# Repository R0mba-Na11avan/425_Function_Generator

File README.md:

# Function Generator (ECE 425)

Firmware for a two-channel function generator built around an ESP32-S3
(N16R8). Per channel, an AD9833 produces the waveform, a TS5A23157 switch picks
the sine/triangle or square path and an AD5452 multiplying DAC sets the
amplitude; one MCP4822 DAC sets both channels' DC offsets (see
`docs/parts.md` for the output stage, `docs/pinout_table.md` for the wiring).
The ESP32 provides three ways to control it:

- **Local:** an ILI9341 LCD dashboard with a rotary encoder and touchscreen
- **AI agents:** an MCP server over Wi-Fi (required for the project)
- **Browser:** a control page at `http://funcgen.local/` on the same Wi-Fi
- **Bluetooth (BLE):** a GATT service a phone can read, write and subscribe to
  (tested with nRF Connect), paired with a passkey shown on the LCD

oui oui baugette

## Architecture

```mermaid
flowchart LR
    LCD["LCD + encoder + touch"]
    MCP["MCP server (HTTP)"]
    WEB["Web page + /api (HTTP)"]
    BLE["BLE (NimBLE)"]
    CTRL["FuncGenController<br/>(mutex, listeners)"]
    FG["FunctionGenerator (CH1)"]
    FG2["FunctionGenerator (CH2)"]
    HW["AD9833 + AD5452 + MCP4822<br/>+ path switch"]

    LCD --> CTRL
    MCP --> CTRL
    WEB --> CTRL
    BLE --> CTRL
    CTRL --> FG --> HW
    CTRL --> FG2 --> HW
```

Every interface is a client of `FuncGenController`. It drives both channels,
serializes access to the hardware (each interface runs in its own task, and
both channels share one SPI bus) and notifies listeners when a channel's state
changes, so the LCD always shows what an agent, phone or browser just set. It
also runs the mirror (LINK: CH2 follows CH1). Nothing outside `core/` touches
`FunctionGenerator` directly.

## Layout

```
425_Function_Generator.ino   creates and wires everything in setup(), loop() deletes itself
src/
  config.h   pins, limits, task settings, network constants
  libs/      vendored third-party libs (AD9833, Adafruit GFX + ILI9341,
             XPT2046_Touchscreen, ArduinoJson) + our own AD5452 and MCP4822 drivers
  core/      FunctionGenerator, FuncGenState, FuncGenController
  core/      ... + net_status.h / ble_status.h (Wi-Fi and BLE state shared by comms and ui)
  core/      ... + safe_pins (control pins to their safe levels, first thing in setup())
  ui/        display_ui (UI task, canvases, listener), dashboard_view (drawing),
             dashboard_logic (layout, formatting, editor), input (encoder + touch),
             input_logic (debounce/accel/tap/hold), boot_screen (Wi-Fi + phones reset countdown).
             the *_logic/_view files are host-tested
  comms/     wifi_manager (+ wifi_logic state machine, provisioning routes),
             http_server, mcp_server, rest_api (web control endpoints),
             api_json (state JSON + Origin check shared by MCP and REST),
             ble_service (+ ble_logic GATT layout and encoding)
  web/       provisioning_html.h (Wi-Fi setup page), index_html.h (control page),
             GENERATED from the top-level web/ folder, don't edit
web/         the pages as plain HTML/CSS/JS (control/, setup/). after a change run
             python tools/embed_web.py (see web/README.md)
tools/       embed_web.py (web/ -> src/web/*_html.h), gen_intellisense.py
```

Dependencies only point downward: `ui`/`comms` -> `core` -> `libs`. `ui` and
`comms` never include each other.

Arduino IDE compiles `src/` recursively but only searches `src/` roots for
headers, so include across folders with relative paths (`"../core/..."`).

## Status

| Part | State |
|---|---|
| `FunctionGenerator` (AD9833 + AD5452 + MCP4822 + path switch) | done (incl. output enable, DC offset, peak limit and limit getters), host-tested, calibration values in `config.h` are placeholders until the output stage is measured |
| `FuncGenController` / `FuncGenState` (two channels, mirror) | done, host-tested |
| `core/safe_pins` (relays open, every generator chip deselected, path switches on the divided path from the top of `setup()`) + both channels reset at boot | done, host-tested against a fake that drops writes to unclaimed pins like ESP32 core 3.x, not tried on hardware yet |
| `ui/input` (encoder via PCNT, button, XPT2046 touch) | done, not tried on hardware yet, touch calibration is a placeholder |
| `ui/display_ui` (dashboard with CH1/CH2 tabs and LINK, editing, info panel with Wi-Fi/phone buttons, remote-change flash, pairing popup) | done, logic and drawing host-tested (screens in `test/build/screens`), not tried on hardware yet |
| `425_Function_Generator.ino` (wiring, boot-time Wi-Fi + phones reset) | done, compiled, not tried on hardware yet |
| `comms/http_server` (shared esp_http_server + route table) | done, host-tested against a fake httpd, not tried on hardware yet |
| `comms/wifi_manager` (STA, AP fallback, setup page, mDNS, NVS) | done, state machine and setup routes host-tested, radio part only compiled, not tried on hardware yet |
| `comms/mcp_server` (JSON-RPC, 9 tools, both channels) | done, host-tested end to end against a fake httpd, not tried on hardware yet |
| `comms/ble_service` (NimBLE GATT, passkey pairing, notifications) | CH1 only (CH2 layout still to be decided), done, encoding and range checks host-tested, the stack part only compiled, not tried on hardware yet |
| `comms/rest_api` + `web/index_html.h` (web control page with a CH1/CH2 switch and Link, `/api/state`, `/api/info`) | done, API host-tested end to end against a fake httpd, page JS only syntax-checked, not tried in a browser against hardware yet |

Suggested order: `config.h` -> display + input -> Wi-Fi + HTTP server (STA, then
AP fallback + provisioning page) -> MCP server -> BLE.

## Design decisions

- **No LVGL.** The dashboard is a single screen drawn directly with Adafruit GFX,
  redrawing only the fields that changed.
- **Two channels:** one controller drives both (`CHANNEL_1`/`CHANNEL_2` in
  code, 1 and 2 in MCP and the web API, where the channel is required so a
  client never changes the wrong output by leaving it out). The LCD shows one
  channel's full dashboard at a time with both channels summed up in a tab row.
- **Mirror (LINK):** CH2 follows CH1's waveform, frequency, amplitude, offset
  and phase; each output's on/off stays its own. Turning it on copies CH1 to
  CH2 right away. While it is on, those CH2 settings are locked everywhere
  (greyed on the LCD, an error over MCP and the web API) instead of quietly
  ending the link. The two AD9833s have their own crystals, so CH2 drifts
  against CH1 in phase; the mirror copies settings, not a phase lock.
- **Wi-Fi:** join the saved network (STA) and fall back to an access point with a
  setup page when that fails, so credentials can be changed without reflashing.
  Credentials are stored in NVS and the device is reachable at `funcgen.local`.
  The setup routes only exist in AP mode. In AP mode with saved credentials it
  tries the saved network again every 5 minutes while nobody is on the AP.
  To change networks, "Change Wi-Fi" in the info panel opens setup mode while
  running (the old network stays saved until a new one is saved). The page is
  never served on the normal network, so a change always needs someone at the
  device.
- **MCP:** Streamable HTTP at `POST /mcp`, stateless, basic tools, **no auth**
  (trusted bench network). Revisit if it is ever exposed more widely.
  Out-of-range values are rejected with a tool error (the LCD clamps instead).
  Requests need `Content-Type: application/json`, and a browser `Origin` must be
  `funcgen.local` or an IP address, so another web site can't drive the generator.
- **Web control page:** served by the generator itself (one embedded HTML file,
  no CDNs, so it also works on the setup AP). It talks to a small JSON API with
  the same request checks and no auth as MCP. Unlike MCP it **clamps** out-of-range
  values (like the knob) and says so. One setting per POST, so the peak rule
  never depends on the order of two changes. The page polls once a second
  instead of holding a socket open. Plain styling for now.
- **BLE:** NimBLE (built into the ESP32 core) through its C API. The Arduino BLE
  wrapper always answers a write with success, so it couldn't reject bad values.
  Every characteristic needs an encrypted, MITM-authenticated link: a new phone
  has to type the 6-digit passkey shown on the LCD, so only someone who can see
  the screen can pair. Up to 3 phones are remembered (oldest dropped). Values are
  fixed-unit integers and out-of-range writes are rejected, like MCP.
- **Limits live in one place** so the LCD, MCP schemas, `get_limits` and the BLE
  range checks can't disagree.
- **Peak limit:** the output can't swing past `OUTPUT_PEAK_MAX_V`, so
  amplitude / 2 + |offset| has to stay below it. The value being changed stops
  at the edge (knob stops, MCP/BLE get an out-of-range error); the other one is
  never moved. `FuncGenLimits::amplitudeFor` / `dcOffsetFor` give the range
  allowed right now.
- **Safe pins at boot:** `holdSafePinStates()` (`core/safe_pins.*`) is the
  first thing `setup()` does: both output relays open, every generator chip
  deselected, both path switches on the divided square path (safe whatever the
  AD9833s powered up making). Both channels' `begin()` follow straight away
  (AD9833 reset to sine and asleep, amplitude 0, offset 0 V, relay open). The
  path switch always moves to the divided path before
  a square starts and back only after it stops, so a 3.3 V square never
  reaches the direct sine/triangle path.
- **Output off** opens the output relay (the BNC is disconnected), puts the
  AD9833 to sleep and sets both DACs to 0 V. The amplitude and offset are kept
  and come back when the output is turned on. The relay opens first when
  turning off and closes last when turning on, and it stays open from power-on
  until the output is turned on, so the start-up glitch never reaches the BNC.

## Build (Arduino IDE)

Board: ESP32S3 Dev Module, Flash 16MB, PSRAM "OPI PSRAM", Partition Scheme
"16M Flash (3MB APP/9.9MB FATFS)" (the default 1.2 MB app partition is too small
once Wi-Fi and BLE are in).

Libraries: everything is vendored in `src/libs`, so nothing needs installing from
the Library Manager. ArduinoJson is v7.4.3 as the official single-header release
(`ArduinoJson-v7.4.3.h`, renamed; the multi-file version needs the library on the
include path, which the IDE doesn't do for `src/libs`). It is used by the Wi-Fi
setup routes and the MCP server, include it as
`#include "../libs/ArduinoJson/ArduinoJson.h"`.

## Using it

- **Channels:** the row under the status bar has a tab per channel (waveform,
  frequency and ON/OFF of each) and a LINK button. The fields below show the
  filled tab's channel. Tap a tab to show that channel, or select the tabs with
  the knob and press to switch.
- **LINK:** tap it (or select it and press) to make CH2 follow CH1. While it is
  lit, CH2's fields read "LINKED", are greyed and can't be edited (change CH1
  instead); CH2's OUTPUT still works on its own. Tap it again to unlink: CH2
  keeps its values.
- **Knob:** turn to pick a field, press to edit it (press on OUTPUT toggles the
  output), turn to change the value. Long press when done (on amplitude, offset
  and waveform a second press works too). Edit mode also ends after 10 s
  without input.
- **Frequency:** while editing, each press moves the underlined digit to the
  next power of 10 (0.1 Hz, 1 Hz, 10 Hz ... 1 MHz, then back to 0.1 Hz); the
  current step shows as "STEP" in the top right. Turning starts from the value
  on screen. In MHz the 0.1 Hz digit isn't shown, so that step acts as 1 Hz.
- **Touch:** tap a field to select it, tap it again to edit, tap a frequency
  digit to step that digit. Tap the status bar for the network info panel.
- **Remote changes:** a field changed over MCP, BLE or the web page flashes
  magenta and an "MCP", "BLE" or "WEB" badge shows in the status bar for a few
  seconds. If you were
  editing that field, editing stops and your next turn starts from the new value.
  A change to the channel that isn't shown flashes its tab instead.
- **Bluetooth:** a Bluetooth icon at the right of the status bar means a phone is
  connected. When a new phone pairs, a full-screen popup shows the code to type
  on the phone; press or tap to cancel (it cancels itself after 30 s).
- **Power-on:** both channels sine, 1 Hz, 1 Vpp, 0 V offset, output OFF, LINK off, CH1 shown.
- **Amplitude and offset** share one limit: the bigger the amplitude, the less
  offset is allowed (and the other way round). The knob just stops at the edge.
- **Info panel buttons:** turn the knob to highlight "Change Wi-Fi", "Forget
  phones" or "close" and press, or tap them.
  - *Change Wi-Fi* (asks first) opens setup mode; the info panel then shows the
    steps. The current network stays saved until you save a new one. In setup
    mode the button becomes *Back to <network>*, which goes straight back. With
    nobody on the setup Wi-Fi it also goes back by itself after 5 minutes.
  - *Forget phones* (asks first) forgets every paired phone and disconnects the
    connected ones. Also remove FuncGen from each phone's Bluetooth settings.
- **Backup reset:** if the screen or touch isn't usable, hold the knob button
  while powering on, through the 3 s countdown. The saved network and the paired
  phones are forgotten and the generator restarts in setup mode.
- **Serial (115200):** prints the firmware version, every network address
  change and BLE pairing results.

## Connecting an agent

Once the generator is on your network (the LCD shows its address):

    claude mcp add --transport http funcgen http://funcgen.local/mcp

If `funcgen.local` doesn't resolve, use the IP from the LCD instead. To poke at it
by hand, run `npx @modelcontextprotocol/inspector`, choose "Streamable HTTP" and
the same URL (the Inspector's default proxy mode works; its direct mode needs
CORS, which this server doesn't offer).

Tools: `set_waveform`, `set_frequency`, `set_amplitude`, `set_phase`,
`set_dc_offset`, `set_output` (each needs `"channel": 1` or `2`), `set_mirror`
(`{"enabled": true}`: CH2 follows CH1), `get_state` (one channel with
`"channel"`, both without), `get_limits` (shared by both channels).

## Web control page

Open `http://funcgen.local/` (or the IP from the LCD) on any phone or laptop on
the same network. In setup mode `/` is the Wi-Fi setup page; the controls are
at `http://192.168.4.1/control` (the setup page links to them).

- **Controls tab:** CH1/CH2 buttons pick the channel the controls change, and
  Link makes CH2 follow CH1 (CH2's controls, except its output, are disabled
  while it is on). Then output on/off, waveform, and fields for frequency (pick
  Hz/kHz/MHz), amplitude, DC offset and phase. A field is sent when you press
  Enter or leave it; Esc undoes the typing. Amplitude and offset show the range
  allowed right now. A value past the edge is clamped and a note says what was
  set. The sketch shows two cycles of the output against the ±peak limit.
- **Device tab:** firmware, Wi-Fi and Bluetooth info. Changing Wi-Fi and
  forgetting phones stay on the LCD only.
- Changes made elsewhere (knob, MCP, BLE, another browser) show up within about
  a second and flash.

API (JSON, the same names as MCP's `get_state`):

| Route | What |
|---|---|
| `GET /api/state` | `{"channels": [{"state": {...}, "ranges": {...}}, ...], "mirror", "output_peak_v"}`, ranges are the ones allowed right now for that channel |
| `POST /api/state` | exactly one setting plus its channel, e.g. `{"channel": 1, "amplitude_vpp": 2.5}`, `{"channel": 2, "waveform": "square"}`, or `{"mirror": true}` on its own. Answers like GET plus `"clamped"` (and a `"note"` when it was). A mirrored CH2 setting while Link is on gets 409. Needs `Content-Type: application/json` |
| `GET /api/info` | firmware, `poll_ms`, Wi-Fi and BLE status |

    curl -X POST -H "Content-Type: application/json" -d "{\"channel\": 1, \"frequency_hz\": 1000}" http://funcgen.local/api/state

## Connecting a phone (BLE)

1. Install **nRF Connect for Mobile** (Nordic Semiconductor, free on iOS and
   Android) and open it. It scans for nearby devices.
2. Tap **Connect** next to `FuncGen-XXXX` (same name as the setup Wi-Fi; the
   info panel shows it).
3. The phone asks to pair: type the code from the LCD popup. This happens once
   per phone.
4. Open the service `54750f00-...` (CH1; CH2 isn't on BLE yet). Each characteristic is labelled. Tap the up
   arrow to write a value, the triple arrow to get live updates.

| UUID | Setting | Bytes | Unit / values | Example |
|---|---|---|---|---|
| `54750f01-…` | waveform | 1 (u8) | 0 sine, 1 square, 2 triangle | `02` |
| `54750f02-…` | frequency | 4 (u32) | 0.01 Hz | 1 kHz = 100000 = `A0 86 01 00` |
| `54750f03-…` | amplitude | 2 (u16) | mVpp (range depends on waveform and offset) | 2.5 Vpp = 2500 = `C4 09` |
| `54750f04-…` | phase | 2 (u16) | 0.01 degree, 0 to 35999 | 90° = 9000 = `28 23` |
| `54750f05-…` | DC offset | 2 (s16) | mV (range depends on amplitude) | -0.25 V = -250 = `06 FF` |
| `54750f06-…` | output | 1 (u8) | 0 off, 1 on | `01` |

Full UUIDs: `54750fXX-f75a-46c0-b78a-746996b46f1a`. Numbers are little-endian
(nRF Connect can also take them as plain numbers if you pick UINT16/UINT32 in the
write dialog). A wrong size or out-of-range value is refused with an ATT error
(0x0D wrong length, 0xFF out of range).

If a phone says it can't connect after the board's phones were forgotten, remove
the board from the phone's Bluetooth settings and pair again.

## Tests

Host tests run the real core, UI logic and vendored libraries on a PC against
fake Arduino/SPI/FreeRTOS headers (`test/fakes`). They check what would reach
the AD9833, the AD5452, the MCP4822 and the path switch, and render the dashboard with the real Adafruit GFX code
to BMP screenshots in `test/build/screens`. The HTTP server, Wi-Fi state machine
and setup routes run against a fake esp_http_server. The BLE value encoding and
range checks run against the real controller; the NimBLE stack itself isn't
faked. The web API runs end to end like MCP; the page's JavaScript is only
syntax-checked (with `node`, if installed), not run. The script also fails if
`src/web/*_html.h` is older than `web/` (run `python tools/embed_web.py`).
Needs Python and g++ (on Windows:
`scoop install mingw`):

    bash test/run_tests.sh

VS Code IntelliSense: `python tools/gen_intellisense.py` writes
`.vscode/compile_commands.json` from the real ESP32-S3 build flags.

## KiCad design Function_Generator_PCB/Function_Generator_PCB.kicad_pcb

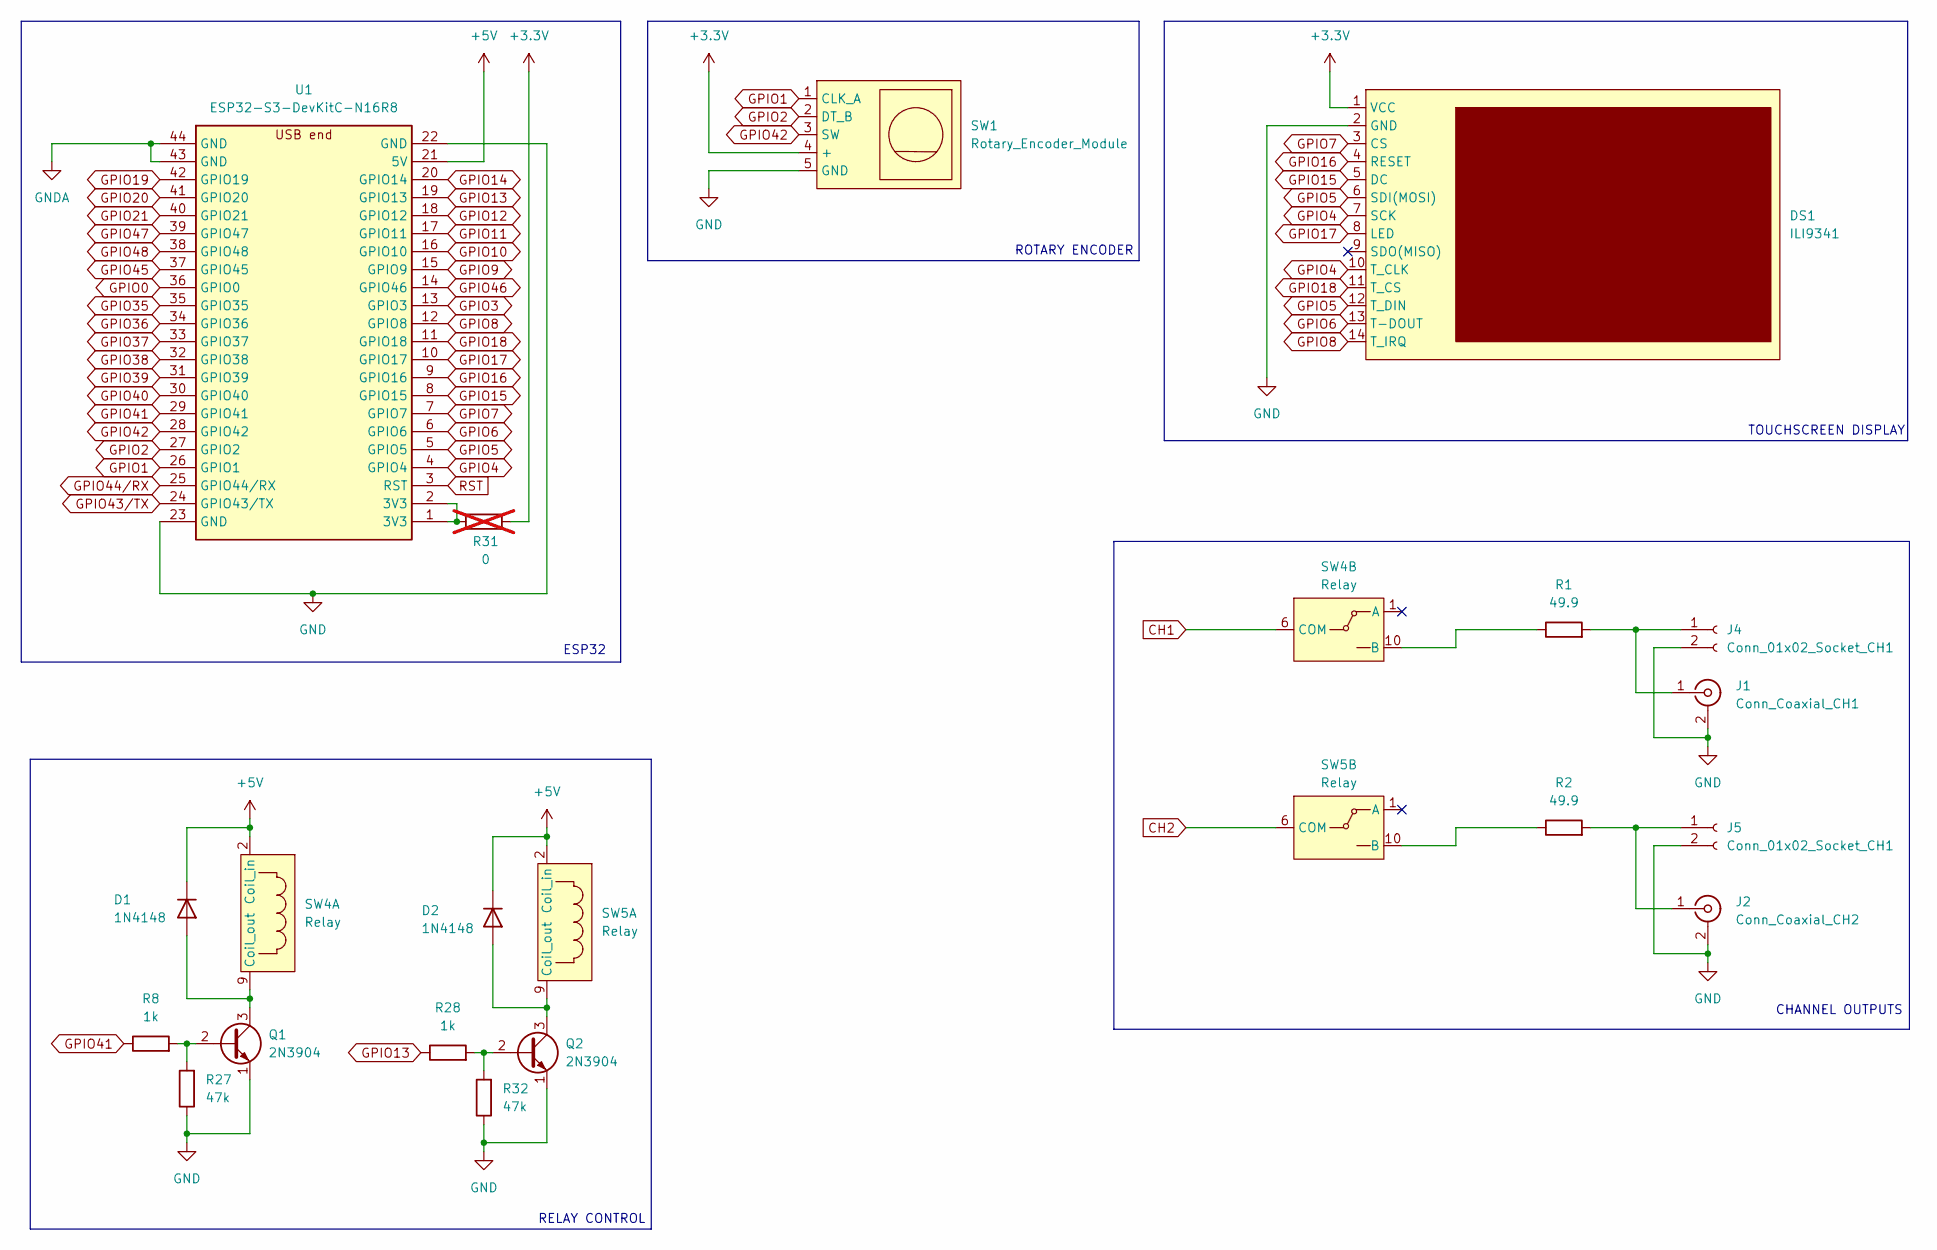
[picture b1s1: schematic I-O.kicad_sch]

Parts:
D1, D2: 1N4148; D_DO-35_SOD27_P7.62mm_Horizontal
DS1: ILI9341; PinSocket_1x14_P2.54mm_Vertical
J1: Conn_Coaxial_CH1; TerminalBlock_MaiXu_MX126-5.0-02P_1x02_P5.00mm
J2: Conn_Coaxial_CH2; TerminalBlock_MaiXu_MX126-5.0-02P_1x02_P5.00mm
J4, J5: Conn_01x02_Socket_CH1; PinSocket_1x02_P2.54mm_Vertical
Q1, Q2: 2N3904; TO-92_Inline
R1, R2: 49.9; R_2512_6332Metric_Pad1.40x3.35mm_HandSolder
R8, R28: 1k; R_0805_2012Metric_Pad1.20x1.40mm_HandSolder
R27, R32: 47k; R_0805_2012Metric_Pad1.20x1.40mm_HandSolder
R31: 0; R_0805_2012Metric_Pad1.20x1.40mm_HandSolder; not fitted
SW1: Rotary_Encoder_Module; PinSocket_1x05_P2.54mm_Vertical
SW4, SW5: Relay; Relay_SPDT_Omron_G5V-1
U1: ESP32-S3-DevKitC-N16R8; ESP32-S3-DevKitC-1_DualUSB

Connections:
+3.3V: DS1.1 (VCC), R31.2, SW1.4 (+); also elsewhere on the board
+5V: D1.1 (K), D2.1 (K), SW4.2 (Coil_in), SW5.2 (Coil_in), U1.21 (5V); also elsewhere on the board
CH1: SW4.6 (COM); also elsewhere on the board
CH2: SW5.6 (COM); also elsewhere on the board
GND: DS1.2 (GND), J1.2 (Ext), J2.2 (Ext), J4.2, J5.2, Q1.1 (E), Q2.1 (E), R27.1, R32.1, SW1.5 (GND), U1.22 (GND), U1.23 (GND), U1.43 (GND), U1.44 (GND); also elsewhere on the board
GPIO0: U1.36 (GPIO0)
GPIO1: SW1.1 (CLK_A), U1.26 (GPIO1)
GPIO2: SW1.2 (DT_B), U1.27 (GPIO2)
GPIO3: U1.13 (GPIO3)
GPIO4: DS1.7 (SCK), DS1.10 (T_CLK), U1.4 (GPIO4)
GPIO5: DS1.6 (SDI(MOSI)), DS1.12 (T_DIN), U1.5 (GPIO5)
GPIO6: DS1.13 (T-DOUT), U1.6 (GPIO6)
GPIO7: DS1.3 (CS), U1.7 (GPIO7)
GPIO8: DS1.14 (T_IRQ), U1.12 (GPIO8)
GPIO9: U1.15 (GPIO9); also elsewhere on the board
GPIO10: U1.16 (GPIO10); also elsewhere on the board
GPIO11: U1.17 (GPIO11); also elsewhere on the board
GPIO12: U1.18 (GPIO12); also elsewhere on the board
GPIO13: R28.1, U1.19 (GPIO13)
GPIO14: U1.20 (GPIO14); also elsewhere on the board
GPIO15: DS1.5 (DC), U1.8 (GPIO15)
GPIO16: DS1.4 (RESET), U1.9 (GPIO16)
GPIO17: DS1.8 (LED), U1.10 (GPIO17)
GPIO18: DS1.11 (T_CS), U1.11 (GPIO18)
GPIO19: U1.42 (GPIO19)
GPIO20: U1.41 (GPIO20)
GPIO21: U1.40 (GPIO21); also elsewhere on the board
GPIO35: U1.35 (GPIO35)
GPIO36: U1.34 (GPIO36)
GPIO37: U1.33 (GPIO37)
GPIO38: U1.32 (GPIO38)
GPIO39: U1.31 (GPIO39); also elsewhere on the board
GPIO40: U1.30 (GPIO40); also elsewhere on the board
GPIO41: R8.1, U1.29 (GPIO41)
GPIO42: SW1.3 (SW), U1.28 (GPIO42)
GPIO43/TX: U1.24 (GPIO43/TX)
GPIO44/RX: U1.25 (GPIO44/RX)
GPIO45: U1.37 (GPIO45)
GPIO46: U1.14 (GPIO46)
GPIO47: U1.39 (GPIO47); also elsewhere on the board
GPIO48: U1.38 (GPIO48)
unnamed: D1.2 (A), Q1.3 (C), SW4.9 (Coil_out)
unnamed: D2.2 (A), Q2.3 (C), SW5.9 (Coil_out)
unnamed: J1.1 (In), J4.1, R1.2
unnamed: J2.1 (In), J5.1, R2.2
unnamed: Q1.2 (B), R8.2, R27.2
unnamed: Q2.2 (B), R28.2, R32.2
unnamed: R31.1, U1.1 (3V3), U1.2 (3V3)
unnamed: R1.1, SW4.10 (B)
unnamed: R2.1, SW5.10 (B)
RST: U1.3 (RST)

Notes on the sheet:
RELAY CONTROL
CHANNEL OUTPUTS
ROTARY ENCODER
ESP32
TOUCHSCREEN DISPLAY

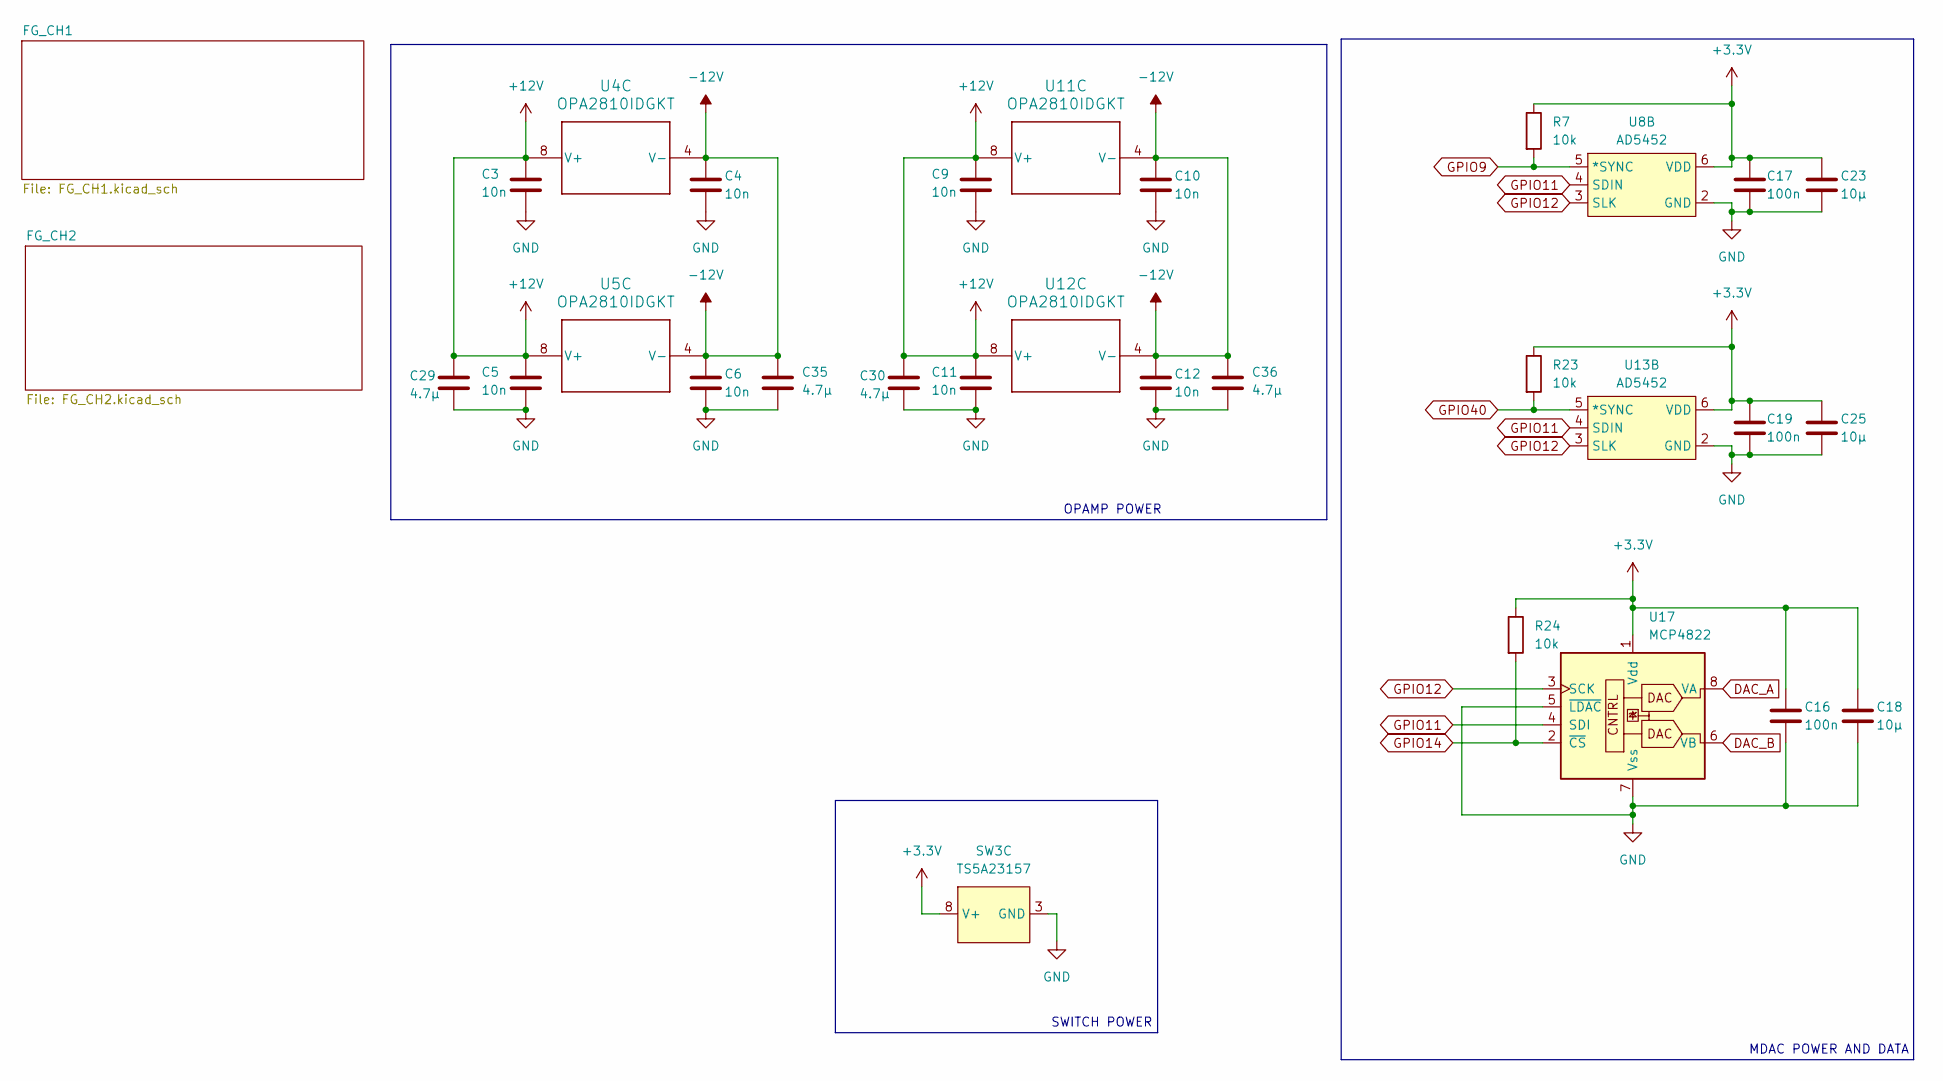
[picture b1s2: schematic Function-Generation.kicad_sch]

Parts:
C3, C4, C5, C6, C9, C10, C11, C12: 10n; C_0805_2012Metric_Pad1.18x1.45mm_HandSolder
C16, C17, C19: 100n; C_0805_2012Metric_Pad1.18x1.45mm_HandSolder
C18, C23, C25: 10μ; C_0805_2012Metric_Pad1.18x1.45mm_HandSolder
C29, C30, C35, C36: 4.7μ; C_1206_3216Metric_Pad1.33x1.80mm_HandSolder
R7, R23, R24: 10k; R_0805_2012Metric_Pad1.20x1.40mm_HandSolder
SW3: TS5A23157; TS5A23157_Module
U4, U5, U11, U12: OPA2810IDGKT; DGK0008A_N
U8, U13: AD5452; RM_8_ADI-M
U17: MCP4822; SOIC8-N_MC_MCH-M

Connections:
+3.3V: C16.1, C17.1, C18.1, C19.1, C23.1, C25.1, R7.1, R23.1, R24.1, SW3.8 (V+), U8.6 (VDD), U13.6 (VDD), U17.1 (Vdd); also elsewhere on the board
+12V: C3.1, C5.1, C9.1, C11.1, C29.1, C30.1, U4.8 (V+), U5.8 (V+), U11.8 (V+), U12.8 (V+); also elsewhere on the board
-12V: C4.1, C6.1, C10.1, C12.1, C35.1, C36.1, U4.4 (V-), U5.4 (V-), U11.4 (V-), U12.4 (V-); also elsewhere on the board
DAC_A: U17.8 (VA); also elsewhere on the board
DAC_B: U17.6 (VB); also elsewhere on the board
GND: C3.2, C4.2, C5.2, C6.2, C9.2, C10.2, C11.2, C12.2, C16.2, C17.2, C18.2, C19.2, C23.2, C25.2, C29.2, C30.2, C35.2, C36.2, SW3.3 (GND), U8.2 (GND), U13.2 (GND), U17.5 (~LDAC), U17.7 (Vss); also elsewhere on the board
GPIO9: R7.2, U8.5 (*SYNC); also elsewhere on the board
GPIO11: U8.4 (SDIN), U13.4 (SDIN), U17.4 (SDI); also elsewhere on the board
GPIO12: U8.3 (SLK), U13.3 (SLK), U17.3 (SCK); also elsewhere on the board
GPIO14: R24.2, U17.2 (~CS); also elsewhere on the board
GPIO40: R23.2, U13.5 (*SYNC); also elsewhere on the board

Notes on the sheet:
OPAMP POWER
MDAC POWER AND DATA
SWITCH POWER

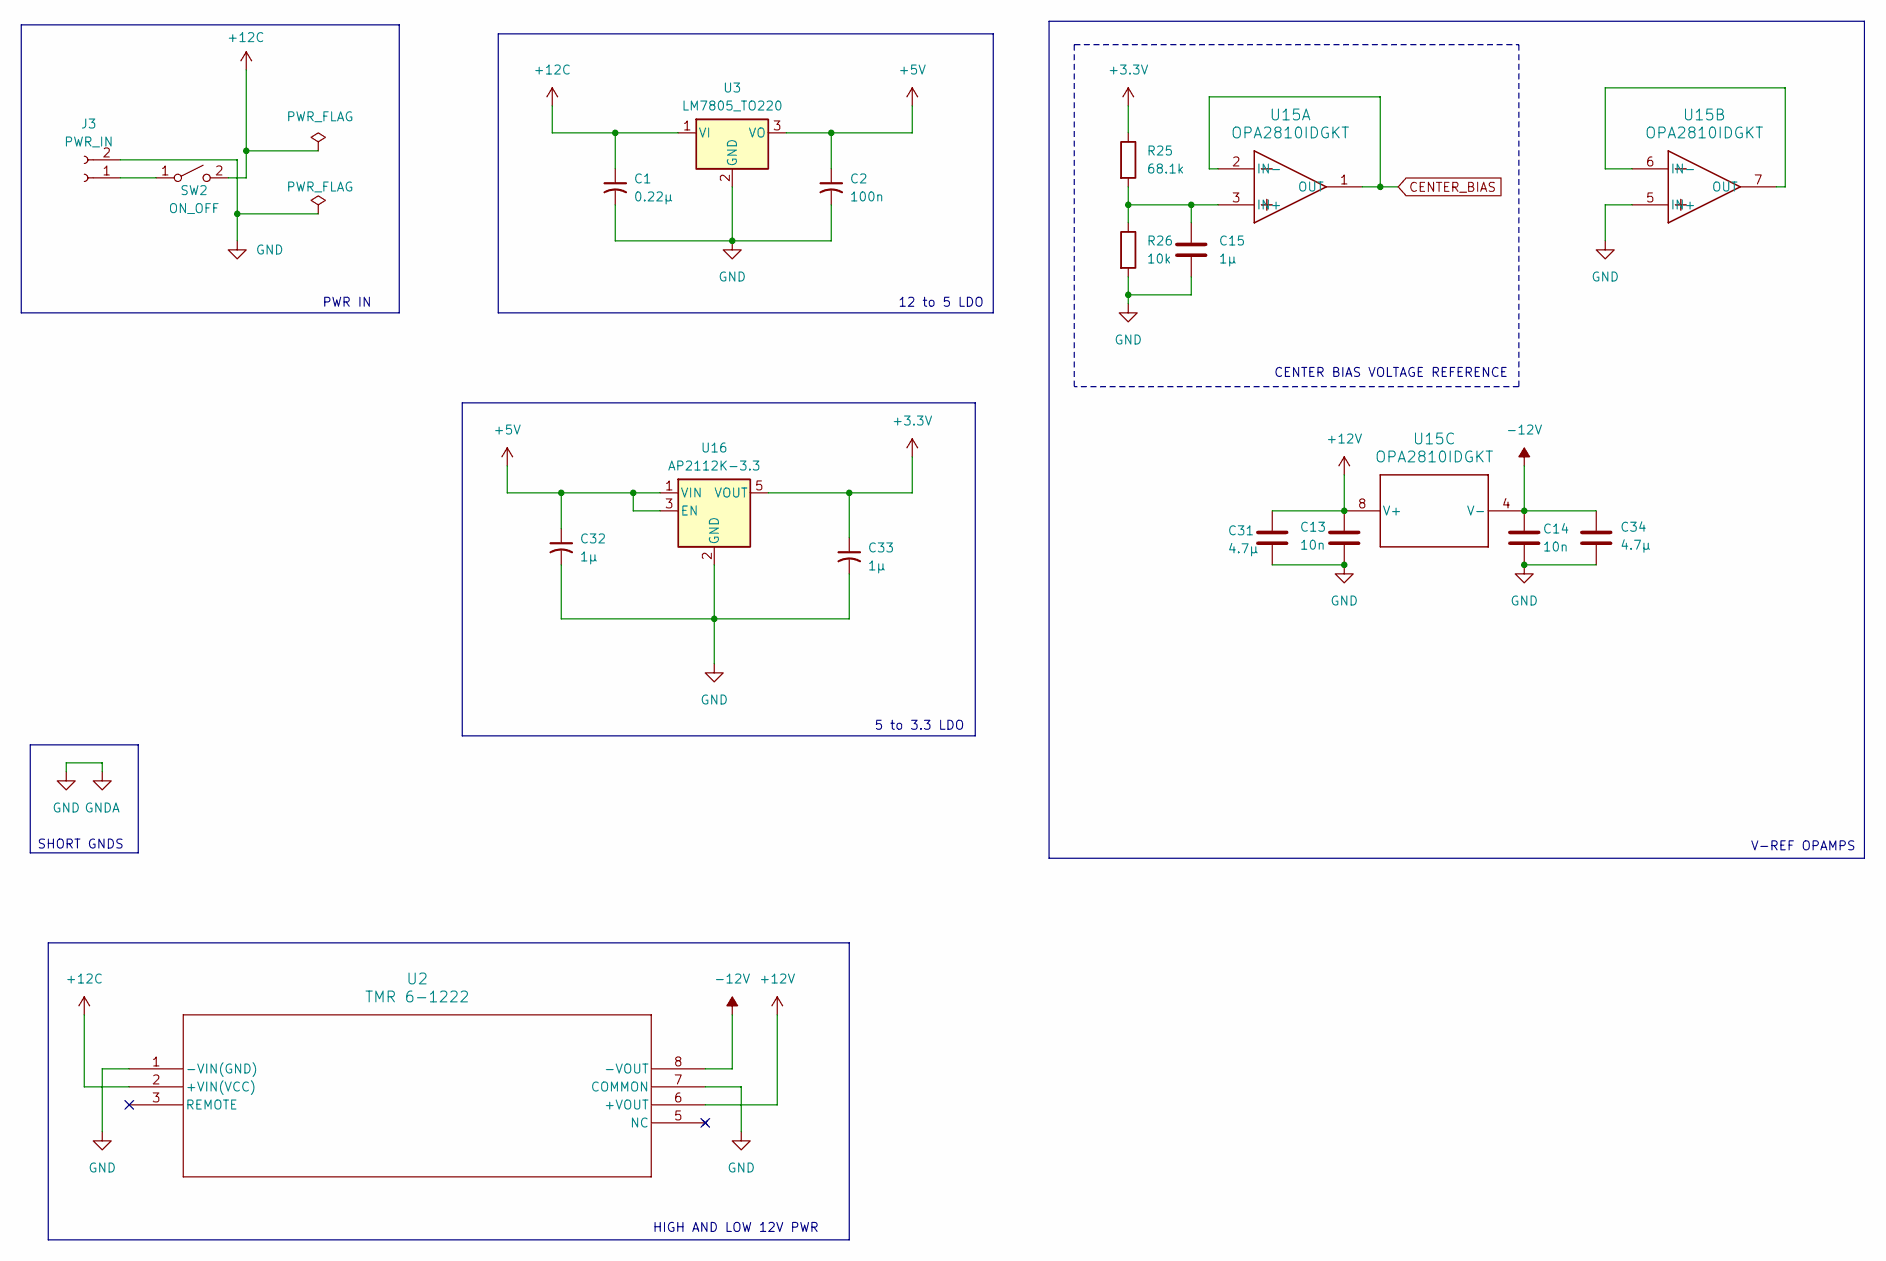
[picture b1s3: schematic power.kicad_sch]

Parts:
C1: 0.22μ; C_0805_2012Metric_Pad1.18x1.45mm_HandSolder
C2: 100n; C_0805_2012Metric_Pad1.18x1.45mm_HandSolder
C13, C14: 10n; C_0805_2012Metric_Pad1.18x1.45mm_HandSolder
C15, C32, C33: 1μ; C_0805_2012Metric_Pad1.18x1.45mm_HandSolder
C31, C34: 4.7μ; C_1206_3216Metric_Pad1.33x1.80mm_HandSolder
J3: PWR_IN; BarrelJack_CUI_PJ-102AH_Horizontal
R25: 68.1k; R_0805_2012Metric_Pad1.20x1.40mm_HandSolder
R26: 10k; R_0805_2012Metric_Pad1.20x1.40mm_HandSolder
SW2: ON_OFF; SolderWire-0.5sqmm_1x02_P4.6mm_D0.9mm_OD2.1mm_Relief
U2: TMR 6-1222; TMR 6_TRP
U3: LM7805_TO220; TO-220-3_Vertical
U15: OPA2810IDGKT; DGK0008A_N
U16: AP2112K-3.3; SOT-23-5

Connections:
+3.3V: C33.1, R25.1, U16.5 (VOUT); also elsewhere on the board
+5V: C2.1, C32.1, U3.3 (VO), U16.1 (VIN), U16.3 (EN); also elsewhere on the board
+12C: C1.1, SW2.2 (B), U2.2 (+VIN(VCC)), U3.1 (VI)
+12V: C13.1, C31.1, U2.6 (+VOUT), U15.8 (V+); also elsewhere on the board
-12V: C14.1, C34.1, U2.8 (-VOUT), U15.4 (V-); also elsewhere on the board
CENTER_BIAS: U15.1 (OUT), U15.2 (IN-); also elsewhere on the board
GND: C1.2, C2.2, C13.2, C14.2, C15.2, C31.2, C32.2, C33.2, C34.2, J3.2, R26.2, U2.1 (-VIN(GND)), U2.7 (COMMON), U3.2 (GND), U15.5 (IN+), U16.2 (GND); also elsewhere on the board
unnamed: J3.1, SW2.1 (A)
unnamed: C15.1, R25.2, R26.1, U15.3 (IN+)
unnamed: U15.6 (IN-), U15.7 (OUT)

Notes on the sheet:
12 to 5 LDO
CENTER BIAS VOLTAGE REFERENCE
5 to 3.3 LDO
PWR IN
V-REF OPAMPS
SHORT GNDS
HIGH AND LOW 12V PWR

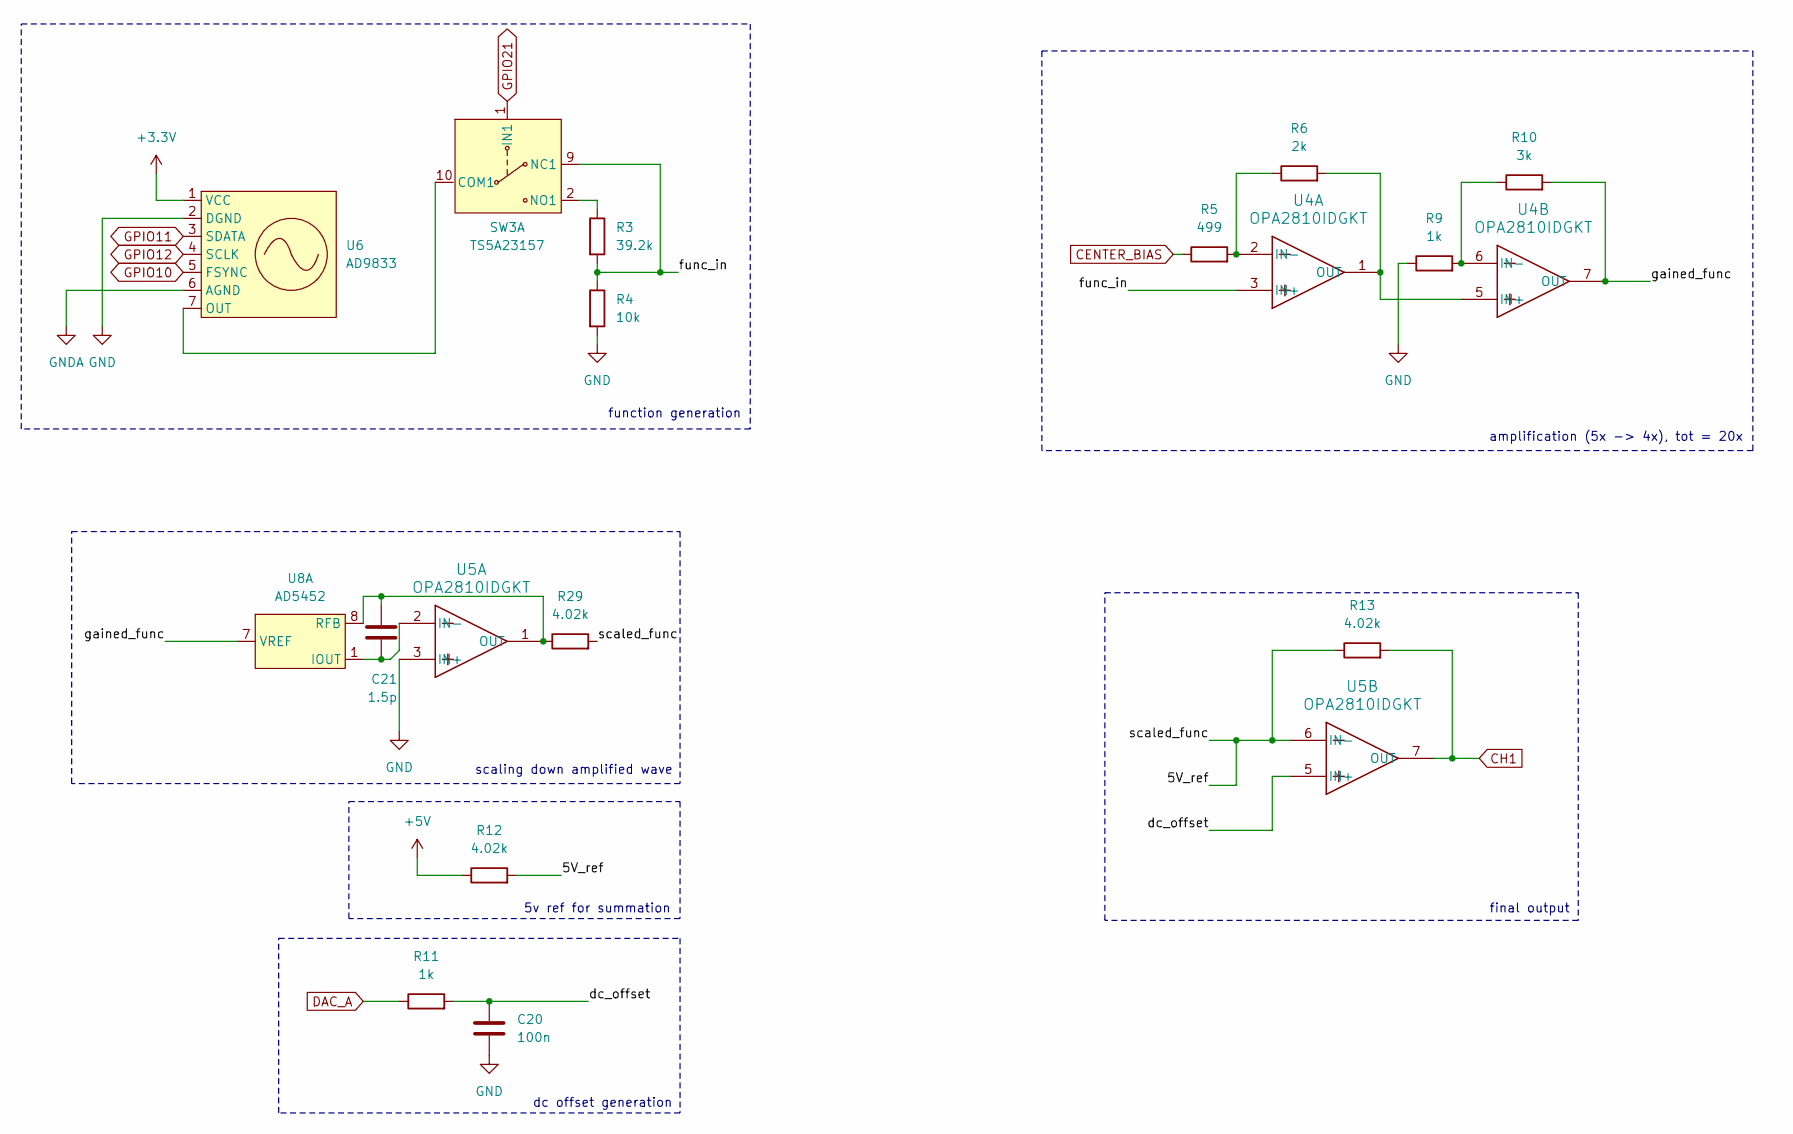
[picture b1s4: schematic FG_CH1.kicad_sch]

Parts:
C20: 100n; C_0805_2012Metric_Pad1.18x1.45mm_HandSolder
C21: 1.5p; C_0805_2012Metric_Pad1.18x1.45mm_HandSolder
R3: 39.2k; R_0805_2012Metric_Pad1.20x1.40mm_HandSolder
R4: 10k; R_0805_2012Metric_Pad1.20x1.40mm_HandSolder
R5: 499; R_0805_2012Metric_Pad1.20x1.40mm_HandSolder
R6: 2k; R_0805_2012Metric_Pad1.20x1.40mm_HandSolder
R9, R11: 1k; R_0805_2012Metric_Pad1.20x1.40mm_HandSolder
R10: 3k; R_0805_2012Metric_Pad1.20x1.40mm_HandSolder
R12, R13, R29: 4.02k; R_0805_2012Metric_Pad1.20x1.40mm_HandSolder
SW3: TS5A23157; TS5A23157_Module
U4, U5: OPA2810IDGKT; DGK0008A_N
U6: AD9833; PinSocket_1x07_P2.54mm_Vertical
U8: AD5452; RM_8_ADI-M

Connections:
+3.3V: U6.1 (VCC); also elsewhere on the board
+5V: R12.1; also elsewhere on the board
/Function_Generation/FG_CH1/5V_ref: R12.2, R13.1, R29.2, U5.6 (IN-)
/Function_Generation/FG_CH1/dc_offset: C20.1, R11.2, U5.5 (IN+)
/Function_Generation/FG_CH1/func_in: R3.2, R4.1, SW3.9 (NC1), U4.3 (IN+)
/Function_Generation/FG_CH1/gained_func: R10.2, U4.7 (OUT), U8.7 (VREF)
CENTER_BIAS: R5.1; also elsewhere on the board
CH1: R13.2, U5.7 (OUT); also elsewhere on the board
DAC_A: R11.1; also elsewhere on the board
GND: C20.2, R4.2, R9.1, U5.3 (IN+), U6.2 (DGND), U6.6 (AGND); also elsewhere on the board
GPIO10: U6.5 (FSYNC); also elsewhere on the board
GPIO11: U6.3 (SDATA); also elsewhere on the board
GPIO12: U6.4 (SCLK); also elsewhere on the board
GPIO21: SW3.1 (IN1); also elsewhere on the board
unnamed: SW3.10 (COM1), U6.7 (OUT)
unnamed: R3.1, SW3.2 (NO1)
unnamed: R5.2, R6.1, U4.2 (IN-)
unnamed: R6.2, U4.1 (OUT), U4.5 (IN+)
unnamed: R9.2, R10.1, U4.6 (IN-)
unnamed: C21.2, U5.2 (IN-), U8.1 (IOUT)
unnamed: C21.1, R29.1, U5.1 (OUT), U8.8 (RFB)

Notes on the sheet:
5v ref for summation
function generation
scaling down amplified wave
final output
amplification (5x -> 4x), tot = 20x
dc offset generation

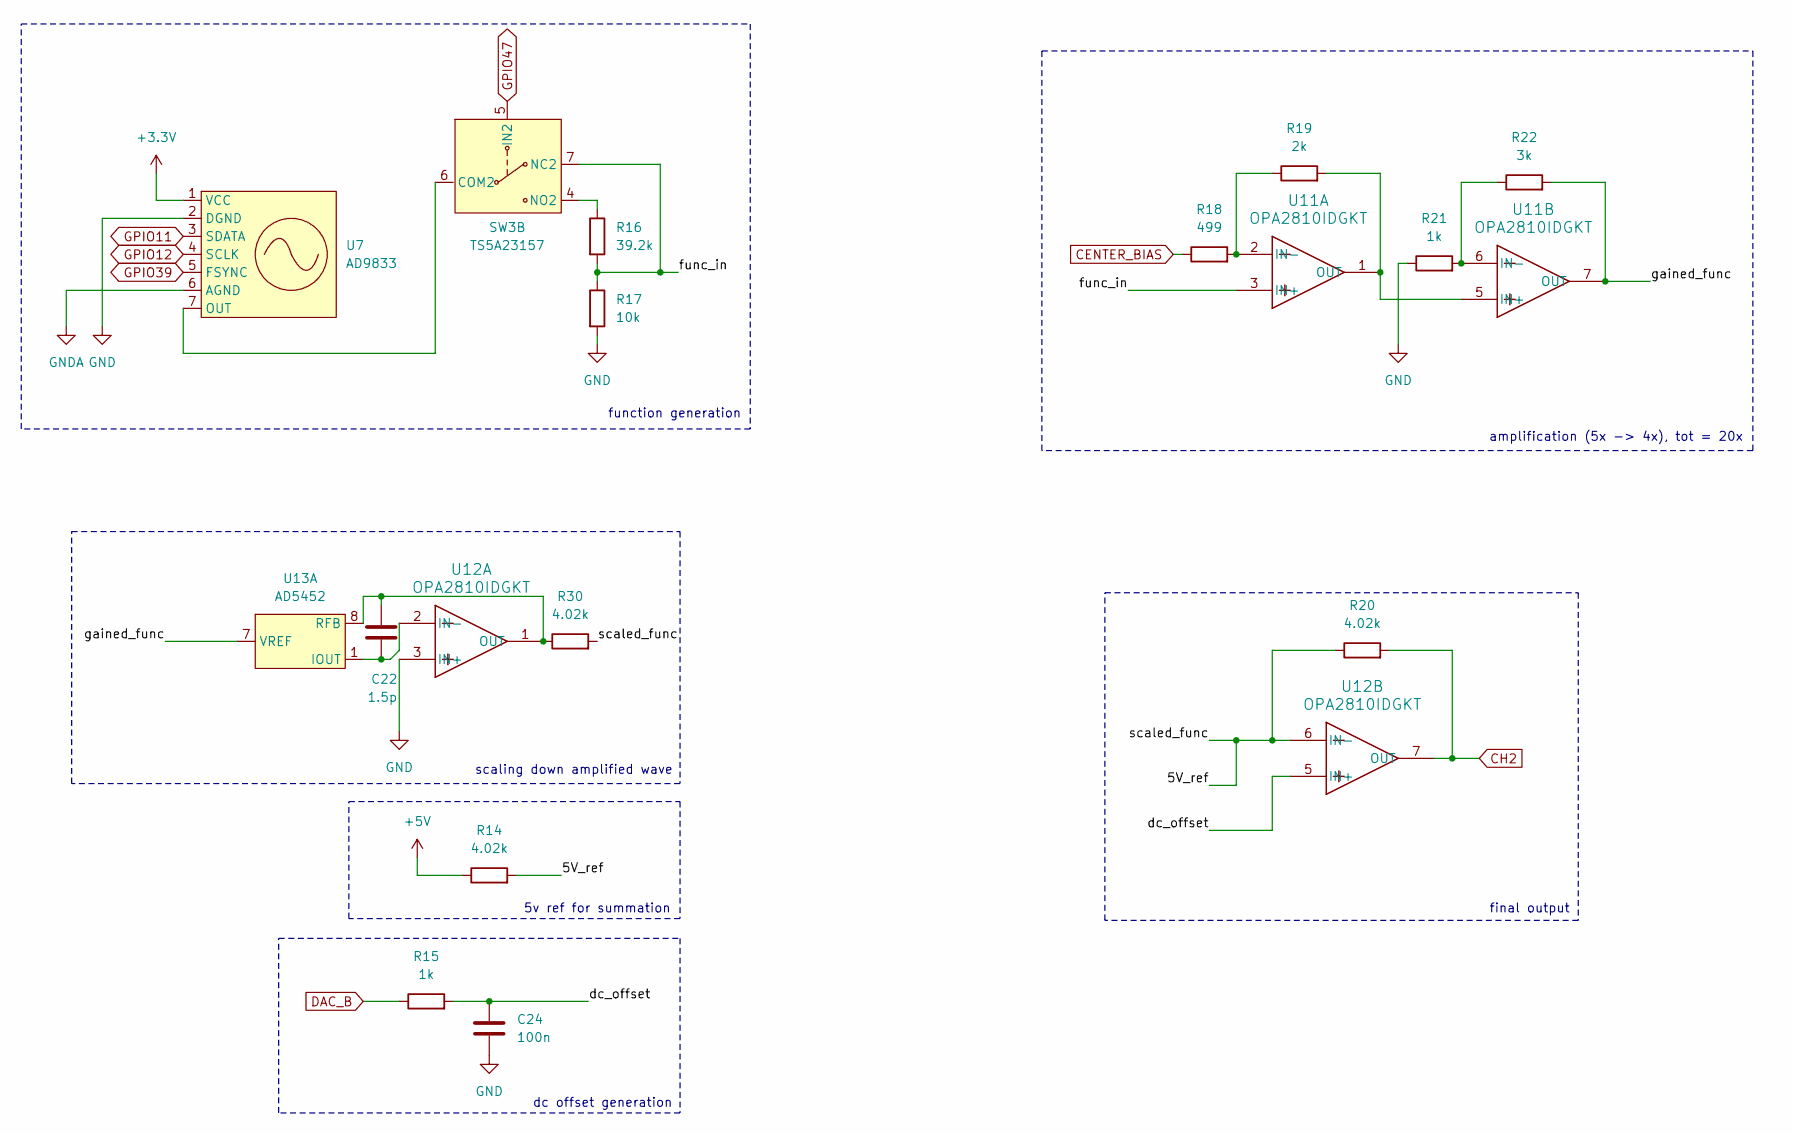
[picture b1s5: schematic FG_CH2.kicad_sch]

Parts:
C22: 1.5p; C_0805_2012Metric_Pad1.18x1.45mm_HandSolder
C24: 100n; C_0805_2012Metric_Pad1.18x1.45mm_HandSolder
R14, R20, R30: 4.02k; R_0805_2012Metric_Pad1.20x1.40mm_HandSolder
R15, R21: 1k; R_0805_2012Metric_Pad1.20x1.40mm_HandSolder
R16: 39.2k; R_0805_2012Metric_Pad1.20x1.40mm_HandSolder
R17: 10k; R_0805_2012Metric_Pad1.20x1.40mm_HandSolder
R18: 499; R_0805_2012Metric_Pad1.20x1.40mm_HandSolder
R19: 2k; R_0805_2012Metric_Pad1.20x1.40mm_HandSolder
R22: 3k; R_0805_2012Metric_Pad1.20x1.40mm_HandSolder
SW3: TS5A23157; TS5A23157_Module
U7: AD9833; PinSocket_1x07_P2.54mm_Vertical
U11, U12: OPA2810IDGKT; DGK0008A_N
U13: AD5452; RM_8_ADI-M

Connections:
+3.3V: U7.1 (VCC); also elsewhere on the board
+5V: R14.1; also elsewhere on the board
/Function_Generation/FG_CH2/5V_ref: R14.2, R20.1, R30.2, U12.6 (IN-)
/Function_Generation/FG_CH2/dc_offset: C24.1, R15.2, U12.5 (IN+)
/Function_Generation/FG_CH2/func_in: R16.2, R17.1, SW3.7 (NC2), U11.3 (IN+)
/Function_Generation/FG_CH2/gained_func: R22.2, U11.7 (OUT), U13.7 (VREF)
CENTER_BIAS: R18.1; also elsewhere on the board
CH2: R20.2, U12.7 (OUT); also elsewhere on the board
DAC_B: R15.1; also elsewhere on the board
GND: C24.2, R17.2, R21.1, U7.2 (DGND), U7.6 (AGND), U12.3 (IN+); also elsewhere on the board
GPIO11: U7.3 (SDATA); also elsewhere on the board
GPIO12: U7.4 (SCLK); also elsewhere on the board
GPIO39: U7.5 (FSYNC); also elsewhere on the board
GPIO47: SW3.5 (IN2); also elsewhere on the board
unnamed: SW3.6 (COM2), U7.7 (OUT)
unnamed: R16.1, SW3.4 (NO2)
unnamed: R18.2, R19.1, U11.2 (IN-)
unnamed: R19.2, U11.1 (OUT), U11.5 (IN+)
unnamed: R21.2, R22.1, U11.6 (IN-)
unnamed: C22.2, U12.2 (IN-), U13.1 (IOUT)
unnamed: C22.1, R30.1, U12.1 (OUT), U13.8 (RFB)

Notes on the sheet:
5v ref for summation
amplification (5x -> 4x), tot = 20x
final output
function generation
scaling down amplified wave
dc offset generation
